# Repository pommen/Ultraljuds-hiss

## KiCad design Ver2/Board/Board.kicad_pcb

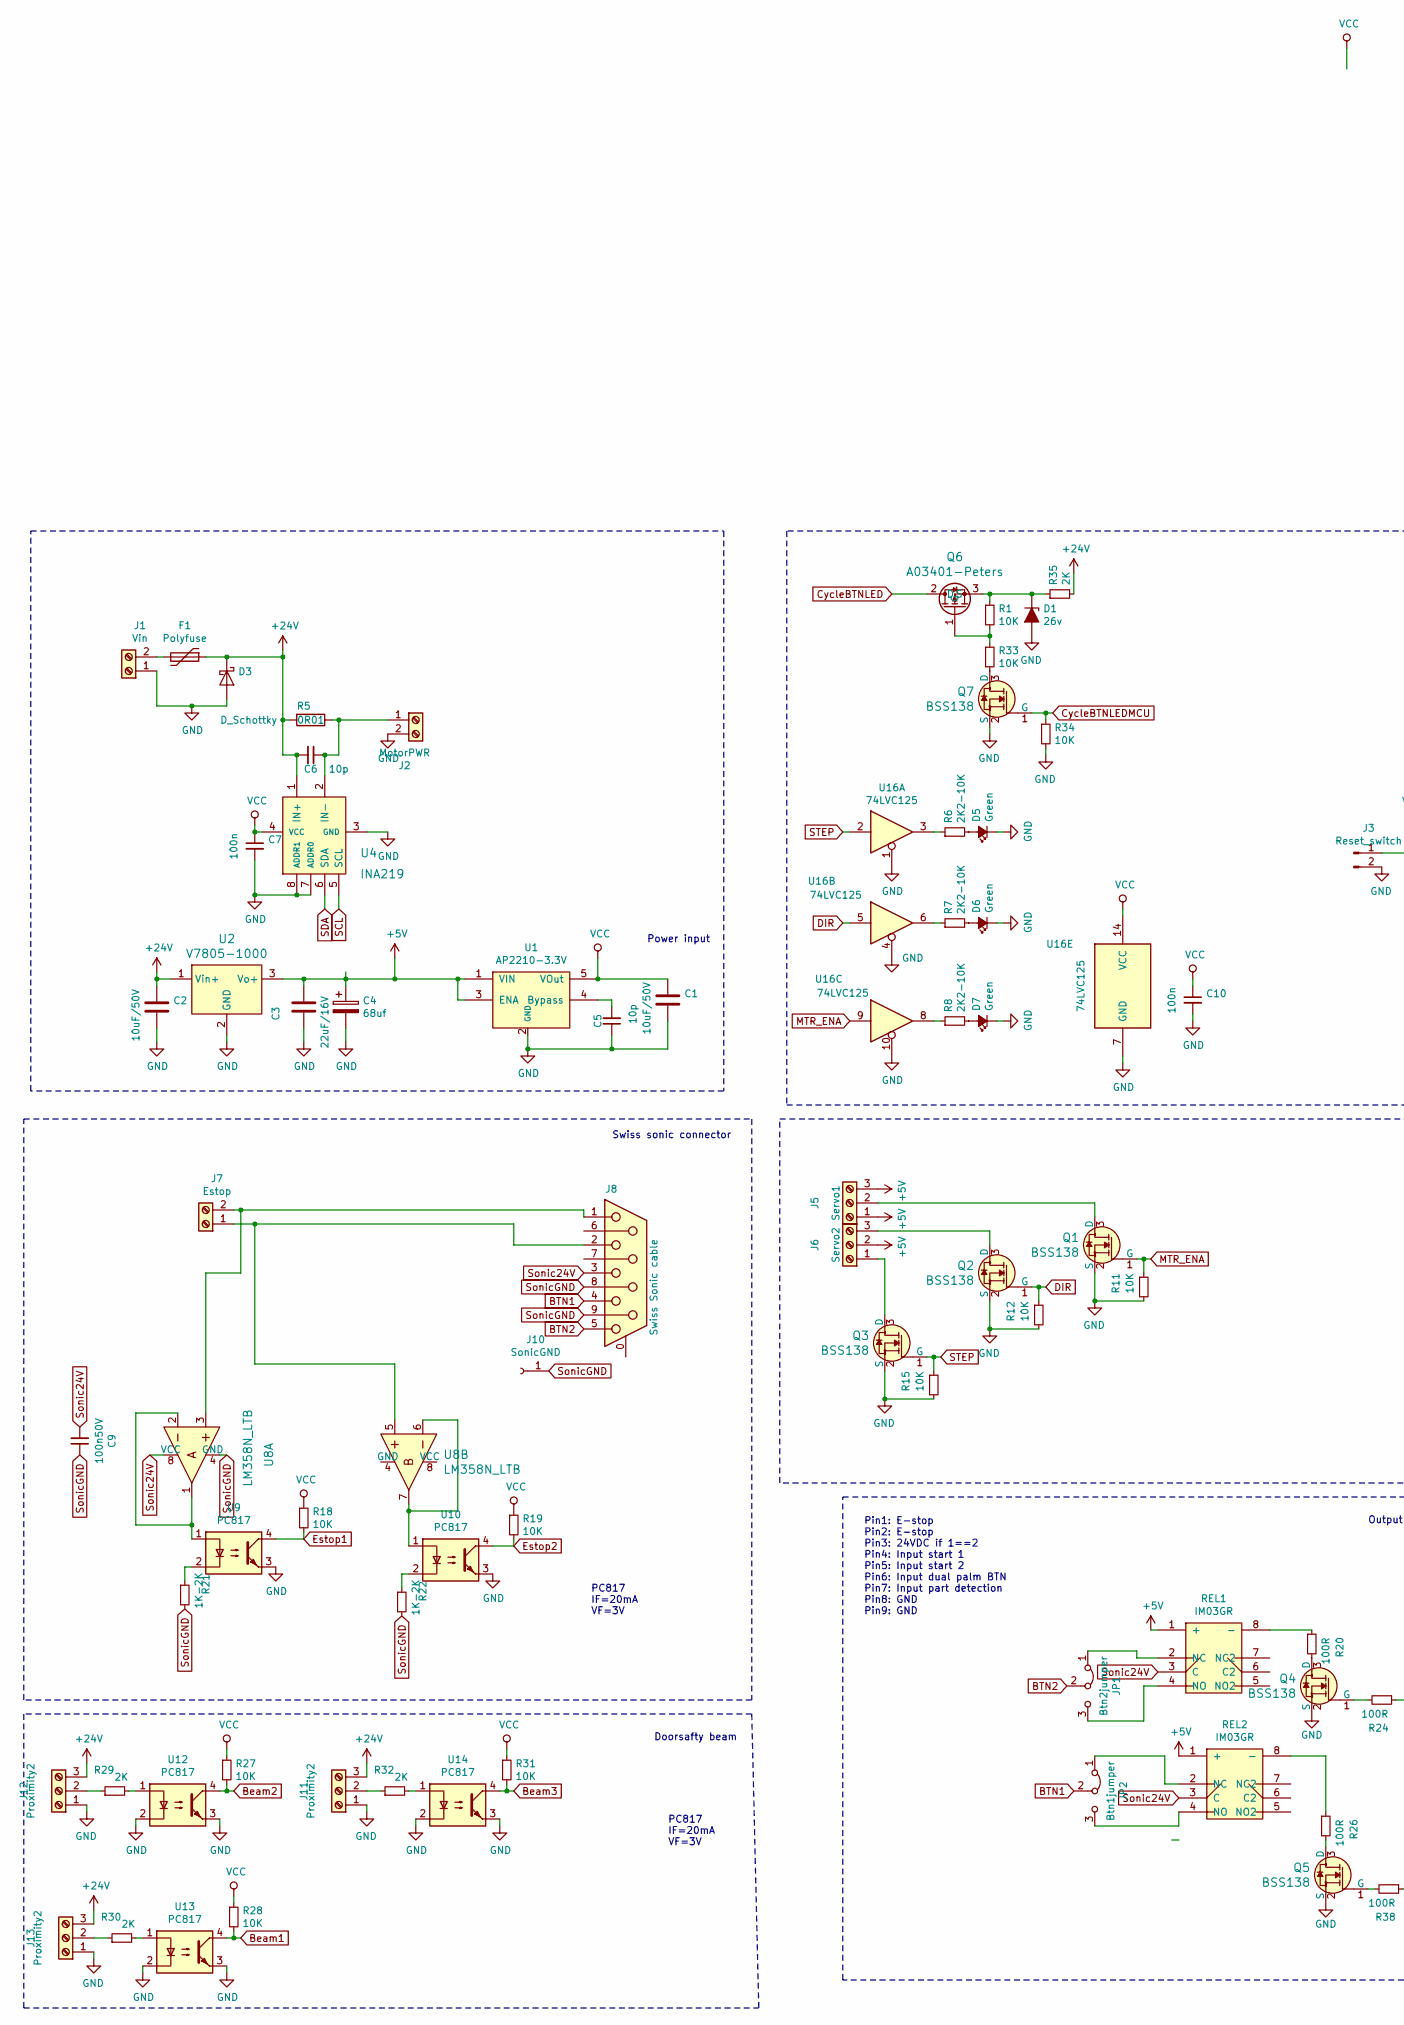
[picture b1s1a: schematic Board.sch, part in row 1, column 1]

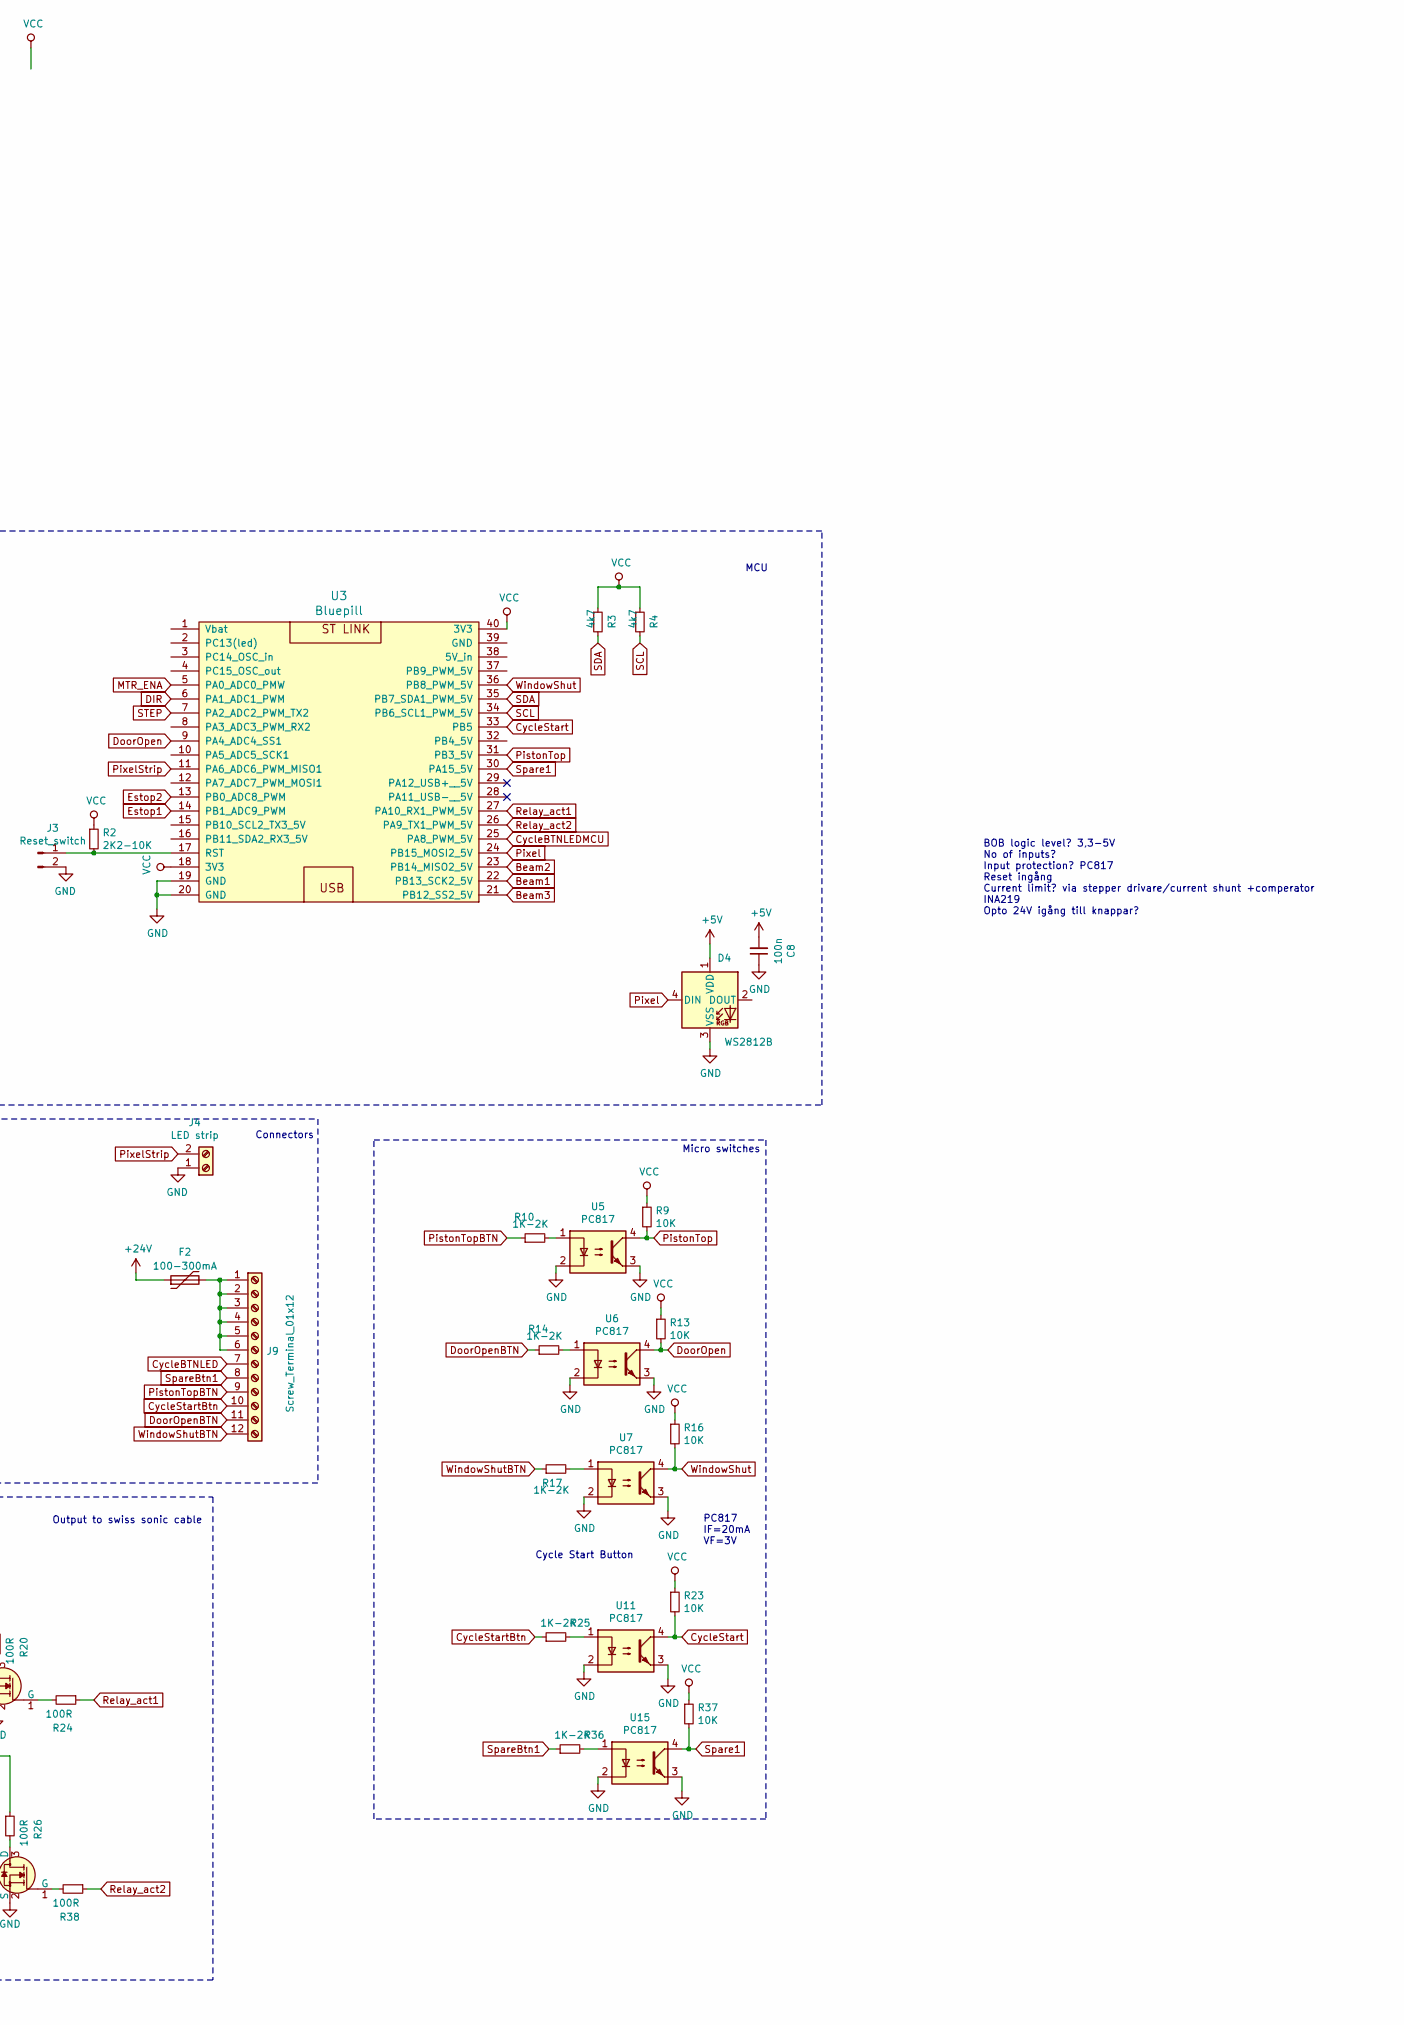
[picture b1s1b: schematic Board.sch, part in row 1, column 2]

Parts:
C1, C2: 10uF/50V; C_2010_5025Metric_Pad1.52x2.65mm_HandSolder
C3: 22uF/16V; C_2010_5025Metric_Pad1.52x2.65mm_HandSolder
C4: 68uf; CP_Elec_6.3x5.4
C5, C6: 10p; C_0805_2012Metric_Pad1.15x1.40mm_HandSolder
C7, C8, C10: 100n; C_0805_2012Metric_Pad1.15x1.40mm_HandSolder
C9: 100n50V; C_0805_2012Metric_Pad1.15x1.40mm_HandSolder
D1: 26v; D_DO-15_P10.16mm_Horizontal
D3: D_Schottky; D_SMB_Handsoldering
D4: WS2812B; LED_WS2812B_PLCC4_5.0x5.0mm_P3.2mm
D5, D6, D7: Green; D_0805_2012Metric_Pad1.15x1.40mm_HandSolder
F1: Polyfuse; LittleFuse_110F_24V
F2: 100-300mA; LittleFuse_110F_24V
J1: Vin; TerminalBlock_bornier-2_P5.08mm
J2: MotorPWR; TerminalBlock_bornier-2_P5.08mm
J3: Reset_switch; PinSocket_1x02_P2.54mm_Vertical
J4: LED strip; TerminalBlock_bornier-2_P5.08mm
J5: Servo1; MKDS1,3-3,81
J6: Servo2; MKDS1,3-3,81
J7: Estop; TerminalBlock_bornier-2_P5.08mm
J8: Swiss Sonic cable; DSUB-9_Male_Horizontal_P2.77x2.84mm_EdgePinOffset4.94mm_Hou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
J9: Screw_Terminal_01x12; TerminalBlock_Phoenix_PT-1,5-12-3.5-H_1x12_P3.50mm_Horizont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
J10: SonicGND; PinHeader_1x01_P2.54mm_Vertical
J11, J12, J13: Proximity2; MKDS1,3-3,81
JP1: Btn2jumper; PinSocket_1x03_P2.54mm_Vertical
JP2: Btn1jumper; PinSocket_1x03_P2.54mm_Vertical
Q1, Q2, Q3, Q4, Q5, Q7: BSS138; SOT-23-3; MPN BSS138; Digi-Key_PN BSS138CT-ND
Q6: A03401-Peters; SOT-23_Handsoldering
R1, R9, R11, R12, R13, R15, R16, R18, R19, R23, R27, R28, R31, R33, R34, R37: 10K; R_0805_2012Metric_Pad1.15x1.40mm_HandSolder
R2, R6, R7, R8: 2K2-10K; R_0805_2012Metric_Pad1.15x1.40mm_HandSolder
R3, R4: 4k7; R_0805_2012Metric_Pad1.15x1.40mm_HandSolder
R5: 0R01; R_2512_6332Metric_Pad1.52x3.35mm_HandSolder
R10, R14, R17, R21, R22, R25, R36: 1K-2K; R_0805_2012Metric_Pad1.15x1.40mm_HandSolder
R20, R24, R26, R38: 100R; R_0805_2012Metric_Pad1.15x1.40mm_HandSolder
R29, R30, R32, R35: 2K; R_0805_2012Metric_Pad1.15x1.40mm_HandSolder
REL1, REL2: IM03GR
U1: AP2210-3.3V; SOT-23-5_HandSoldering
U2: V7805-1000; 3-SIP_Module_V7805-1000; MPN V7805-1000; Digi-Key_PN 102-1715-ND
U3: Bluepill
U4: INA219; TSOT-23-8_HandSoldering
U5, U6, U7, U9, U10, U11, U12, U13, U14, U15: PC817; DIP-4_W7.62mm
U8: LM358N_LTB; DIP-8_W7.62mm; MPN LM358N; Digi-Key_PN LM358NFS-ND
U16: 74LVC125; SOIC-14_3.9x8.7mm_P1.27mm

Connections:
+5V: C3.1, C4.1, C8.2, D4.1 (VDD), J5.1, J5.3, J6.2, REL1.1 (+), REL2.1 (+), U1.1 (VIN), U1.3 (ENA), U2.3 (Vo+)
+24V: C2.1, C6.2, D3.1 (K), F1.1, F2.1, J11.3, J12.3, J13.3, R5.2, R35.2, U2.1 (Vin+), U4.1 (IN+)
BTN1: J8.4, JP2.2 (C)
BTN2: J8.5, JP1.2 (C)
Beam1: R28.2, U3.22 (PB13_SCK2_5V), U13.4
Beam2: R27.2, U3.23 (PB14_MISO2_5V), U12.4
Beam3: R31.2, U3.21 (PB12_SS2_5V), U14.4
CycleBTNLED: J9.7, Q6.2 (D)
CycleBTNLEDMCU: Q7.1 (G), R34.1, U3.25 (PA8_PWM_5V)
CycleStart: R23.2, U3.33 (PB5), U11.4
CycleStartBtn: J9.10, R25.1
DIR: Q2.1 (G), R12.1, U3.6 (PA1_ADC1_PWM), U16.5
DoorOpen: R13.2, U3.9 (PA4_ADC4_SS1), U6.4
DoorOpenBTN: J9.11, R14.1
Estop1: R18.2, U3.14 (PB1_ADC9_PWM), U9.4
Estop2: R19.2, U3.13 (PB0_ADC8_PWM), U10.4
GND: C1.2, C2.2, C3.2, C4.2, C5.1, C7.2, C8.1, C10.2, D1.2 (A), D3.2 (A), D4.3 (VSS), D5.1 (K), D6.1 (K), D7.1 (K), J1.1, J2.2, J3.2, J4.1, J11.1, J12.1, J13.1, Q1.2 (S), Q2.2 (S), Q3.2 (S), Q4.2 (S), Q5.2 (S), Q7.2 (S), R11.2, R12.2, R15.2, R34.2, U1.2 (GND), U2.2 (GND), U3.19 (GND), U3.20 (GND), U4.3 (GND), U4.7 (ADDR0), U4.8 (ADDR1), U5.2, U5.3, U6.2, U6.3, U7.2, U7.3, U9.3, U10.3, U11.2, U11.3, U12.2, U12.3, U13.2, U13.3, U14.2, U14.3, U15.2, U15.3, U16.1, U16.4, U16.7 (GND), U16.10
MTR_ENA: Q1.1 (G), R11.1, U3.5 (PA0_ADC0_PMW), U16.9
unnamed: C5.2, U1.4 (Bypass)
unnamed: C6.1, J2.1, R5.1, U4.2 (IN-)
unnamed: D1.1 (K), Q6.3 (S), R1.1, R35.1
unnamed: D5.2 (A), R6.2
unnamed: D6.2 (A), R7.2
unnamed: D7.2 (A), R8.2
unnamed: F1.2, J1.2
unnamed: F2.2, J9.1, J9.2, J9.3, J9.4, J9.5, J9.6
unnamed: J3.1, R2.2, U3.17 (RST)
unnamed: J5.2, Q1.3 (D)
unnamed: J6.1, Q3.3 (D)
unnamed: J6.3, Q2.3 (D)
unnamed: J7.1, J8.2, U8.5
unnamed: J7.2, J8.1, U8.3
unnamed: J11.2, R32.1
unnamed: J12.2, R29.1
unnamed: J13.2, R30.1
unnamed: JP1.1 (A), REL1.2 (NC)
unnamed: JP1.3 (B), REL1.4 (NO)
unnamed: JP2.1 (A), REL2.2 (NC)
unnamed: JP2.3 (B), REL2.4 (NO)
unnamed: Q4.1 (G), R24.2
unnamed: Q4.3 (D), R20.2
unnamed: Q5.1 (G), R38.2
unnamed: Q5.3 (D), R26.2
unnamed: Q6.1 (G), R1.2, R33.1
unnamed: Q7.3 (D), R33.2
unnamed: R6.1, U16.3
unnamed: R7.1, U16.6
unnamed: R8.1, U16.8
unnamed: R10.2, U5.1
unnamed: R14.2, U6.1
unnamed: R17.2, U7.1
unnamed: R20.1, REL1.8 (-)
unnamed: R21.1, U9.2
unnamed: R22.1, U10.2
unnamed: R25.2, U11.1
unnamed: R26.1, REL2.8 (-)
unnamed: R29.2, U12.1
unnamed: R30.2, U13.1
unnamed: R32.2, U14.1
unnamed: R36.2, U15.1
unnamed: U8.1, U8.2, U9.1
unnamed: U8.6, U8.7, U10.1
PistonTop: R9.2, U3.31 (PB3_5V), U5.4
PistonTopBTN: J9.9, R10.1
Pixel: D4.4 (DIN), U3.24 (PB15_MOSI2_5V)
PixelStrip: J4.2, U3.11 (PA6_ADC6_PWM_MISO1)
Relay_act1: R24.1, U3.27 (PA10_RX1_PWM_5V)
Relay_act2: R38.1, U3.26 (PA9_TX1_PWM_5V)
SCL: R4.2, U3.34 (PB6_SCL1_PWM_5V), U4.5 (SCL)
SDA: R3.2, U3.35 (PB7_SDA1_PWM_5V), U4.6 (SDA)
STEP: Q3.1 (G), R15.1, U3.7 (PA2_ADC2_PWM_TX2), U16.2
Sonic24V: C9.2, J8.3, REL1.3 (C), REL2.3 (C), U8.8 (VCC)
SonicGND: C9.1, J8.8, J8.9, J10.1, R21.2, R22.2, U8.4 (GND)
Spare1: R37.2, U3.30 (PA15_5V), U15.4
SpareBtn1: J9.8, R36.1
VCC: C1.1, C7.1, C10.1, R2.1, R3.1, R4.1, R9.1, R13.1, R16.1, R18.1, R19.1, R23.1, R27.1, R28.1, R31.1, R37.1, U1.5 (VOut), U3.18 (3V3), U3.40 (3V3), U4.4 (VCC), U16.14 (VCC)
WindowShut: R16.2, U3.36 (PB8_PWM_5V), U7.4
WindowShutBTN: J9.12, R17.1

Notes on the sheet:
BOB logic level? 3,3-5V No of inputs? Input protection? PC817 Reset ingång Current limit? via stepper drivare/current shunt +comperator INA219 Opto 24V igång till knappar?
Output to swiss sonic cable
Micro switches
PC817 IF=20mA VF=3V
Cycle Start Button
MCU
Pin1: E-stop Pin2: E-stop Pin3: 24VDC if 1==2 Pin4: Input start 1 Pin5: Input start 2 Pin6: Input dual palm BTN Pin7: Input part detection Pin8: GND Pin9: GND
Connectors
Swiss sonic connector
Doorsafty beam
Power input

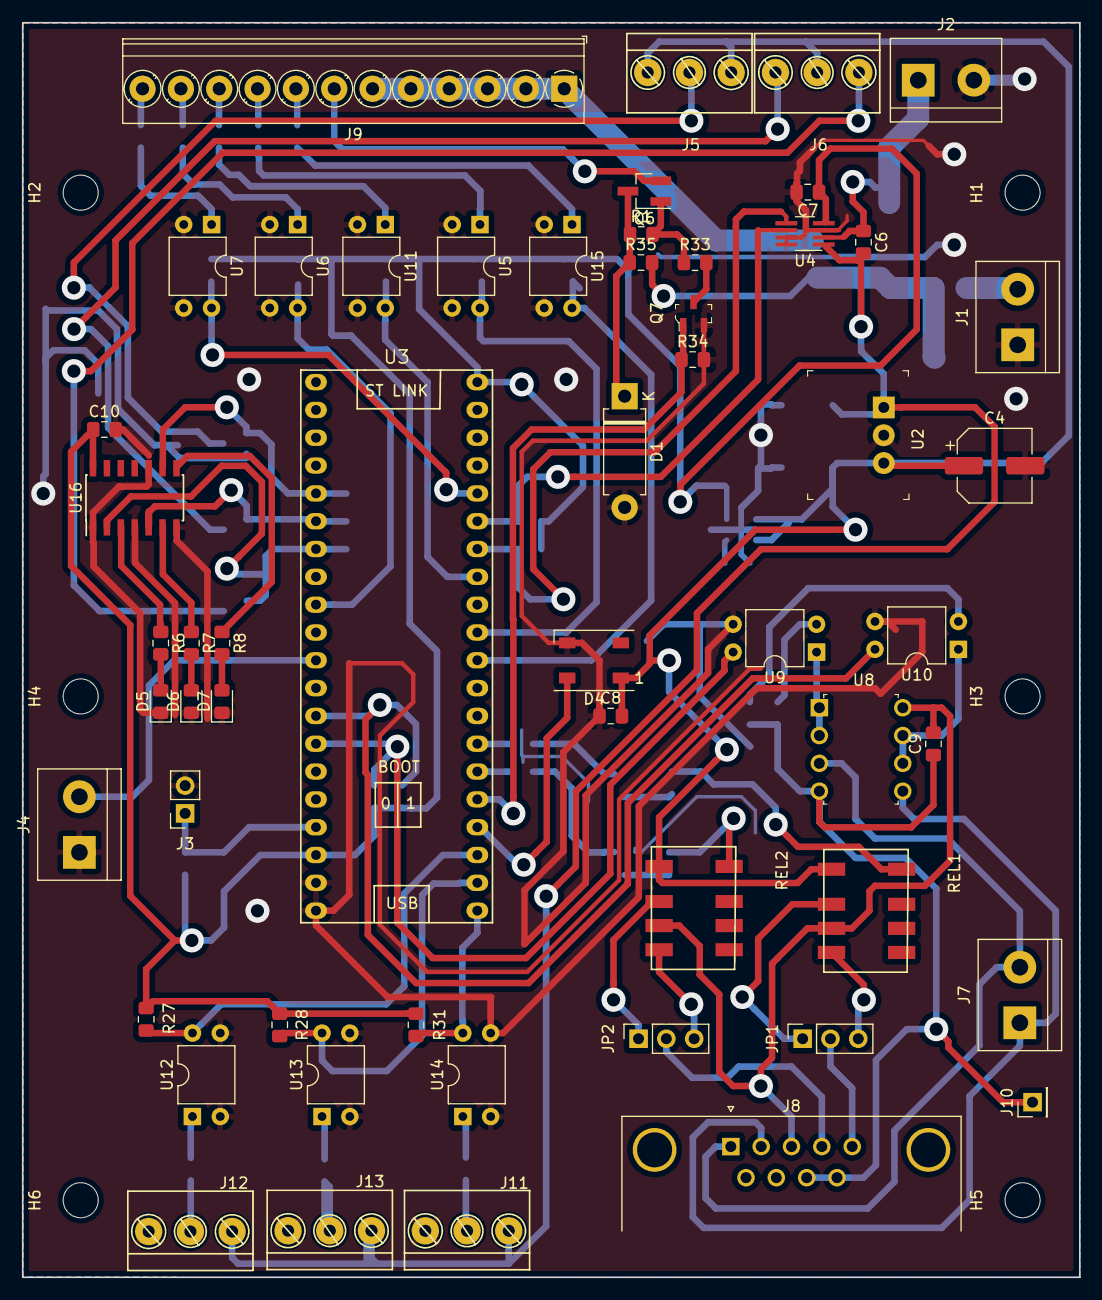
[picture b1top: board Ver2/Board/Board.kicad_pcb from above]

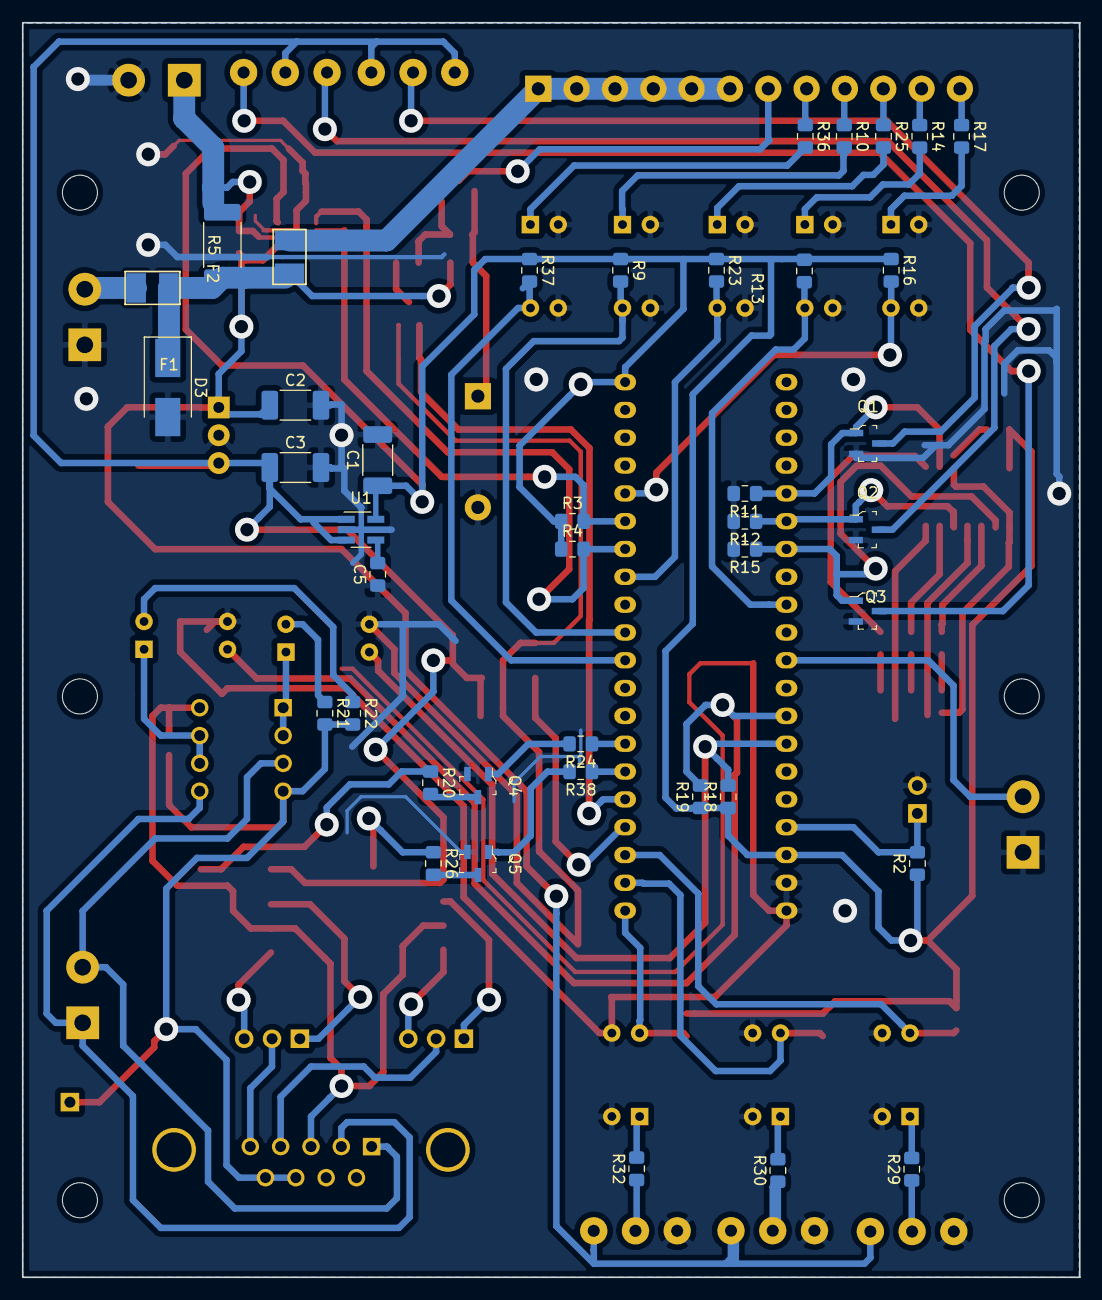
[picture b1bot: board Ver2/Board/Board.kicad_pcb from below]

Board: 2 copper layers, 96.5 x 114.6 mm, 102 parts (41 on the bottom side), 78 nets.

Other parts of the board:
H1, H2, H3, H4, H5, H6: MountingHole; MountingHole_3.2mm_M3

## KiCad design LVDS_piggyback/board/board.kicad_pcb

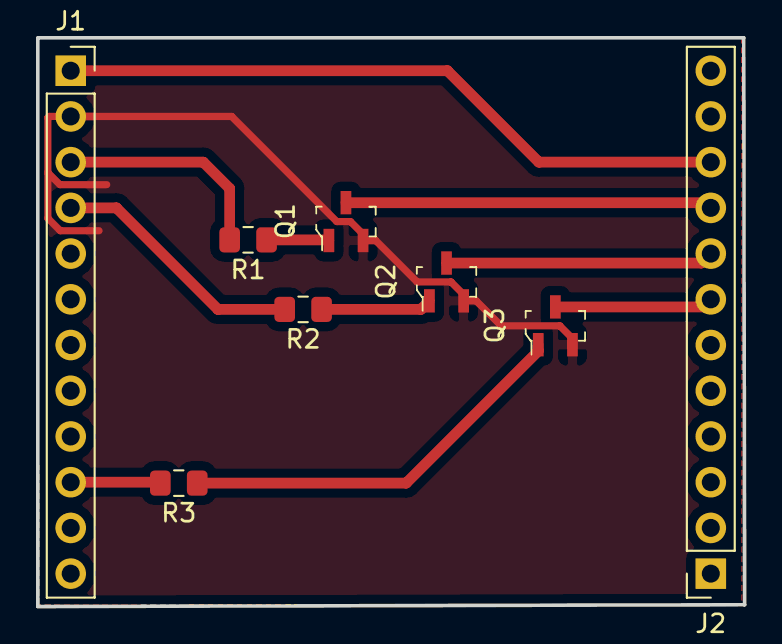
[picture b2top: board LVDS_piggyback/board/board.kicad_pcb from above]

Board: 2 copper layers, 39.3 x 31.6 mm, 8 parts (0 on the bottom side), 11 nets.

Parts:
J1: PiggybackIN; PinSocket_1x12_P2.54mm_Vertical
J2: PiggybackOUT; PinSocket_1x12_P2.54mm_Vertical
Q1, Q2, Q3: BSS138; SOT-23-3
R1, R2, R3: R; R_0805_2012Metric_Pad1.15x1.40mm_HandSolder

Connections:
DIR: J1.4, R2.2
ENA: J1.10, R3.2
GND: J1.2, Q1.2, Q2.2, Q3.2
unnamed: J2.7, Q3.3
unnamed: J2.8, Q2.3
unnamed: J2.9, Q1.3
unnamed: Q1.1, R1.1
unnamed: Q2.1, R2.1
unnamed: Q3.1, R3.1
VCC: J1.1, J2.10
step: J1.3, R1.2

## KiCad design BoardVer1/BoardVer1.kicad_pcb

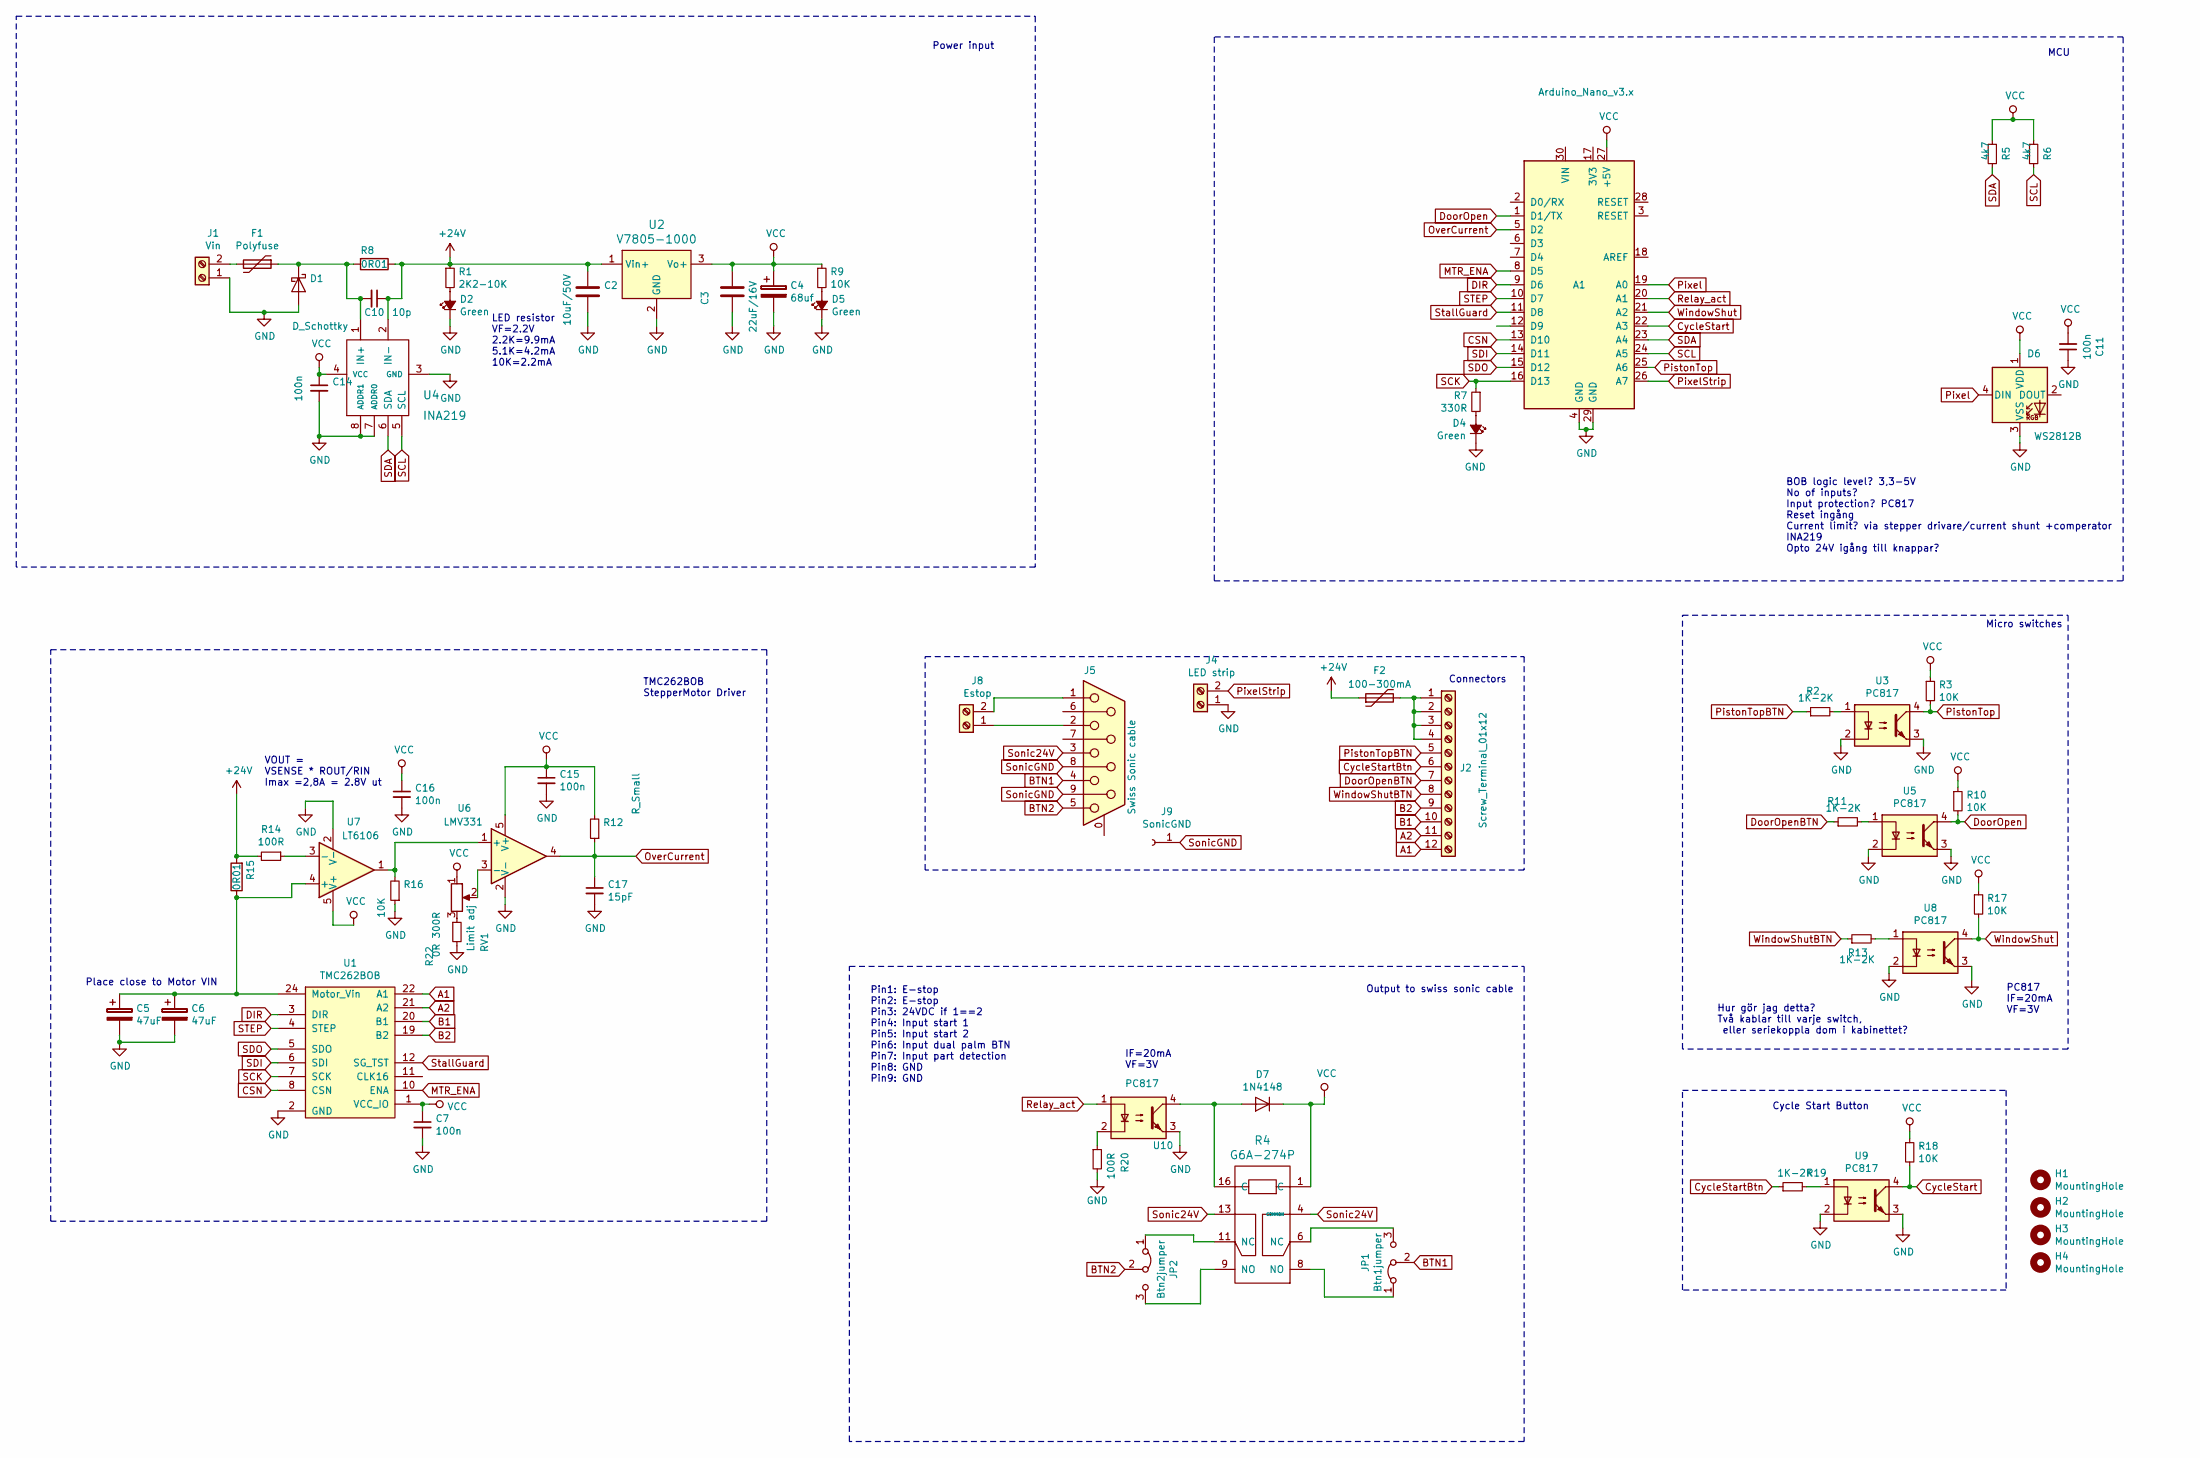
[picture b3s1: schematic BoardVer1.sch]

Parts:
A1: Arduino_Nano_v3.x; Arduino_Nano
C2: 10uF/50V; C_2010_5025Metric_Pad1.52x2.65mm_HandSolder
C3: 22uF/16V; C_2010_5025Metric_Pad1.52x2.65mm_HandSolder
C4: 68uf; CP_Elec_6.3x5.4
C5, C6: 47uF; CP_Elec_6.3x5.4
C7, C11, C14, C15, C16: 100n; C_0805_2012Metric_Pad1.15x1.40mm_HandSolder
C10: 10p; C_0805_2012Metric_Pad1.15x1.40mm_HandSolder
C17: 15pF; C_0805_2012Metric_Pad1.15x1.40mm_HandSolder
D1: D_Schottky; D_SMB_Handsoldering
D2, D4, D5: Green; D_0805_2012Metric_Pad1.15x1.40mm_HandSolder
D6: WS2812B; LED_WS2812B_PLCC4_5.0x5.0mm_P3.2mm
D7: 1N4148; D_DO-35_SOD27_P7.62mm_Horizontal
F1: Polyfuse; LittleFuse_110F_24V
F2: 100-300mA; LittleFuse_110F_24V
H1, H2, H3, H4: MountingHole; MountingHole_3.2mm_M3
J1: Vin; TerminalBlock_bornier-2_P5.08mm
J2: Screw_Terminal_01x12; TerminalBlock_Phoenix_PT-1,5-12-3.5-H_1x12_P3.50mm_Horizont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
J4: LED strip; TerminalBlock_bornier-2_P5.08mm
J5: Swiss Sonic cable; DSUB-9_Male_Horizontal_P2.77x2.84mm_EdgePinOffset4.94mm_Hou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
J8: Estop; TerminalBlock_bornier-2_P5.08mm
J9: SonicGND; PinHeader_1x01_P2.54mm_Vertical
JP1: Btn1jumper; PinSocket_1x03_P2.54mm_Vertical
JP2: Btn2jumper; PinSocket_1x03_P2.54mm_Vertical
R1: 2K2-10K; R_0805_2012Metric_Pad1.15x1.40mm_HandSolder
R2, R11, R13, R19: 1K-2K; R_0805_2012Metric_Pad1.15x1.40mm_HandSolder
R3, R9, R10, R16, R17, R18: 10K; R_0805_2012Metric_Pad1.15x1.40mm_HandSolder
R4: G6A-274P; OMRON_G6A-274P-ST
R5, R6: 4k7; R_0805_2012Metric_Pad1.15x1.40mm_HandSolder
R7: 330R; R_0805_2012Metric_Pad1.15x1.40mm_HandSolder
R8, R15: 0R01; R_2512_6332Metric_Pad1.52x3.35mm_HandSolder
R12: R_Small; R_0805_2012Metric_Pad1.15x1.40mm_HandSolder
R14, R20: 100R; R_0805_2012Metric_Pad1.15x1.40mm_HandSolder
R22: 0R 300R; R_0805_2012Metric_Pad1.15x1.40mm_HandSolder
RV1: Limit adj; Potentiometer_ACP_CA9-H5_Horizontal
U1: TMC262BOB
U2: V7805-1000; 3-SIP_Module_V7805-1000; MPN V7805-1000; Digi-Key_PN 102-1715-ND
U3, U5, U8, U9, U10: PC817; DIP-4_W7.62mm
U4: INA219; TSOT-23-8_HandSoldering
U6: LMV331; SOT-23-5_HandSoldering
U7: LT6106; SOT-23-5

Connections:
+24V: C2.1, C10.1, F2.1, R1.1, R8.1, R14.2, R15.2, U2.1 (Vin+), U4.2 (IN-)
A1: J2.12, U1.22 (A1)
A2: J2.11, U1.21 (A2)
B1: J2.10, U1.20 (B1)
B2: J2.9, U1.19 (B2)
BTN1: J5.4, JP1.2 (C)
BTN2: J5.5, JP2.2 (C)
CSN: A1.13 (D10), U1.8 (CSN)
CycleStart: A1.22 (A3), R18.2, U9.4
CycleStartBtn: J2.6, R19.1
DIR: A1.9 (D6), U1.3 (DIR)
DoorOpen: A1.1 (D1/TX), R10.2, U5.4
DoorOpenBTN: J2.7, R11.1
GND: A1.4 (GND), A1.29 (GND), C2.2, C3.2, C4.2, C5.2, C6.2, C7.2, C11.1, C14.2, C15.2, C16.2, C17.2, D1.2 (A), D2.1 (K), D4.1 (K), D5.1 (K), D6.3 (VSS), J1.1, J4.1, R16.1, R20.2, R22.2, U1.2 (GND), U1.9 (GND), U1.13 (GND), U1.14 (GND), U1.15 (GND), U1.16 (GND), U1.17 (GND), U1.18 (GND), U1.23 (GND), U2.2 (GND), U3.2, U3.3, U4.3 (GND), U4.7 (ADDR0), U4.8 (ADDR1), U5.2, U5.3, U6.2 (V-), U7.2 (V-), U8.2, U8.3, U9.2, U9.3, U10.3
MTR_ENA: A1.8 (D5), U1.10 (ENA)
unnamed: C5.1, C6.1, R15.1, U1.24 (Motor_Vin), U7.4 (+)
unnamed: C10.2, D1.1 (K), F1.1, R8.2, U4.1 (IN+)
unnamed: D2.2 (A), R1.2
unnamed: D4.2 (A), R7.2
unnamed: D5.2 (A), R9.2
unnamed: D7.2 (A), R4.16 (C), U10.4
unnamed: F1.2, J1.2
unnamed: F2.2, J2.1, J2.2, J2.3, J2.4
unnamed: J5.1, J8.2
unnamed: J5.2, J8.1
unnamed: JP1.1 (A), R4.8 (NO)
unnamed: JP1.3 (B), R4.6 (NC)
unnamed: JP2.1 (A), R4.11 (NC)
unnamed: JP2.3 (B), R4.9 (NO)
unnamed: R2.2, U3.1
unnamed: R11.2, U5.1
unnamed: R13.2, U8.1
unnamed: R14.1, U7.3 (-)
unnamed: R16.2, U6.1 (+), U7.1
unnamed: R19.2, U9.1
unnamed: R20.1, U10.2
unnamed: R22.1, RV1.3
unnamed: RV1.2, U6.3 (-)
OverCurrent: A1.5 (D2), C17.1, R12.1, U6.4
PistonTop: A1.25 (A6), R3.2, U3.4
PistonTopBTN: J2.5, R2.1
Pixel: A1.19 (A0), D6.4 (DIN)
PixelStrip: A1.26 (A7), J4.2
Relay_act: A1.20 (A1), U10.1
SCK: A1.16 (D13), R7.1, U1.7 (SCK)
SCL: A1.24 (A5), R6.2, U4.5 (SCL)
SDA: A1.23 (A4), R5.2, U4.6 (SDA)
SDI: A1.14 (D11), U1.6 (SDI)
SDO: A1.15 (D12), U1.5 (SDO)
STEP: A1.10 (D7), U1.4 (STEP)
Sonic24V: J5.3, R4.4 (COMMON), R4.13
SonicGND: J5.8, J5.9, J9.1
StallGuard: A1.11 (D8), U1.12 (SG_TST)
VCC: A1.27 (+5V), C3.1, C4.1, C7.1, C11.2, C14.1, C15.1, C16.1, D6.1 (VDD), D7.1 (K), R3.1, R4.1 (C), R5.1, R6.1, R9.1, R10.1, R12.2, R17.1, R18.1, RV1.1, U1.1 (VCC_IO), U2.3 (Vo+), U4.4 (VCC), U6.5 (V+), U7.5 (V+)
WindowShut: A1.21 (A2), R17.2, U8.4
WindowShutBTN: J2.8, R13.1

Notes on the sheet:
BOB logic level? 3,3-5V No of inputs? Input protection? PC817 Reset ingång Current limit? via stepper drivare/current shunt +comperator INA219 Opto 24V igång till knappar?
Place close to Motor VIN
LED resistor VF=2.2V 2.2K=9.9mA 5.1K=4.2mA 10K=2.2mA
Output to swiss sonic cable
TMC262BOB StepperMotor Driver
Micro switches
PC817 IF=20mA VF=3V
IF=20mA VF=3V
Cycle Start Button
VOUT = VSENSE * ROUT/RIN Imax =2,8A = 2.8V ut
MCU
Power input
Connectors
Pin1: E-stop Pin2: E-stop Pin3: 24VDC if 1==2 Pin4: Input start 1 Pin5: Input start 2 Pin6: Input dual palm BTN Pin7: Input part detection Pin8: GND Pin9: GND
Hur gör jag detta? Två kablar till varje switch, eller seriekoppla dom i kabinettet?

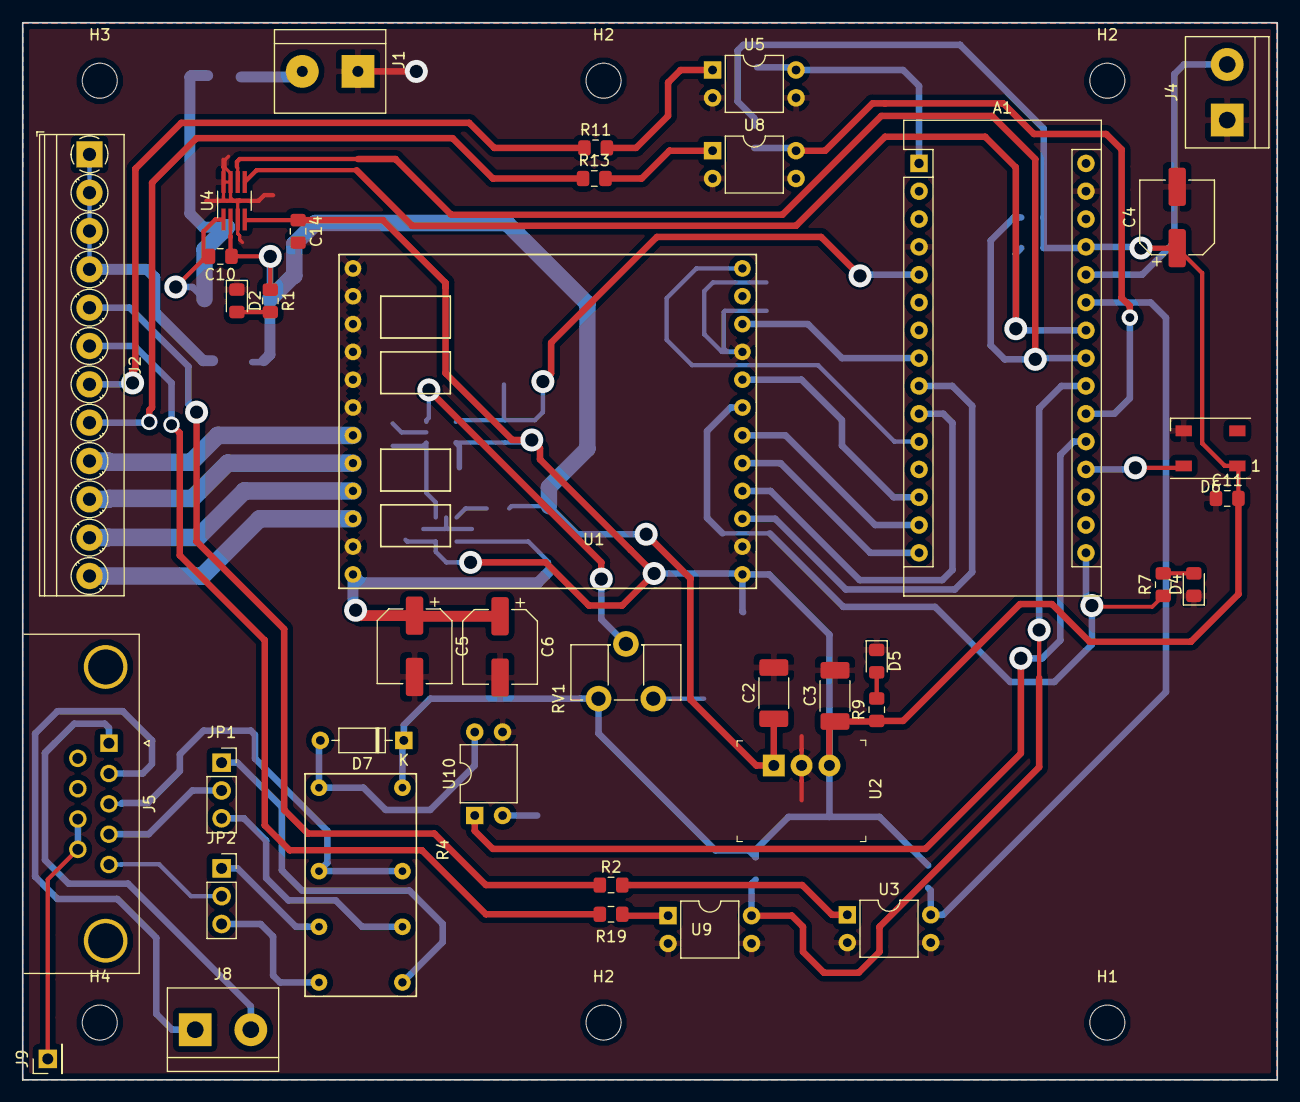
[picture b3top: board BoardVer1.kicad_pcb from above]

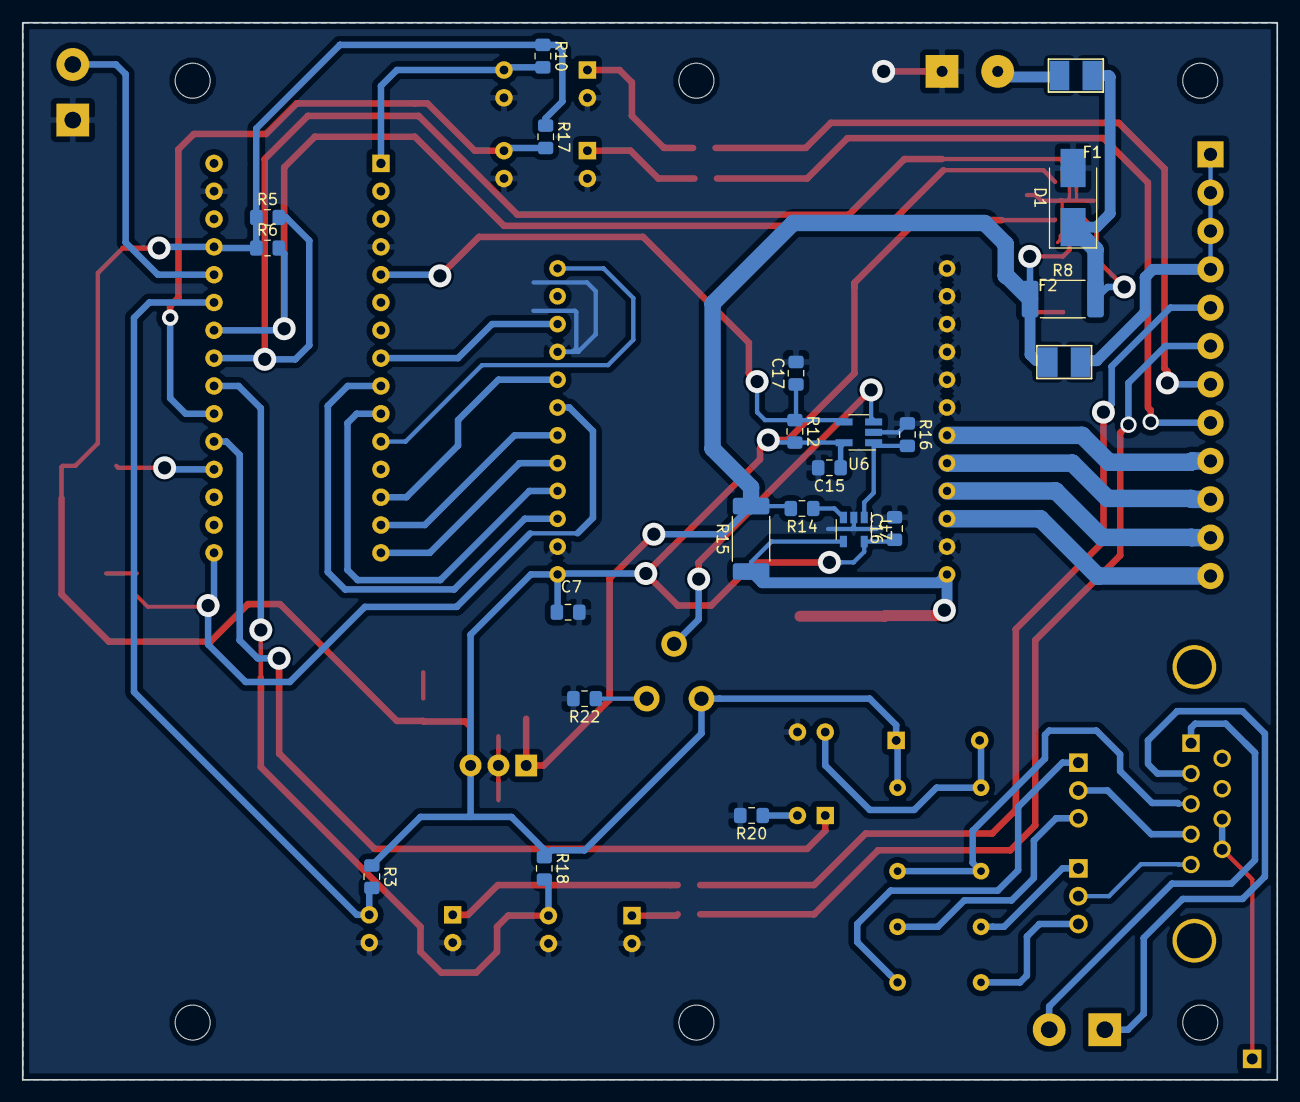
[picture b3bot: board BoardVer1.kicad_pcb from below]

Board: 2 copper layers, 114.6 x 96.5 mm, 67 parts (22 on the bottom side), 56 nets.

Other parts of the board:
H2#2, H2#3: MountingHole; MountingHole_3.2mm_M3

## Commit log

2019-01-21 First layout complete
2019-01-21 TMC262BOB datasheet
2019-01-23 Less vias
2019-01-26 Better layout
2019-01-27 BOM and polish
2019-01-29 grbr
2019-03-21 distance beam
2019-03-22 Layout begun
2019-03-24 routing
2019-03-25 layout done
